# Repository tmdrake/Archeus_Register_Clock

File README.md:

# Archeus_Register_Clock
Driver and Clock for a mechanical tele-register clock.

See video: https://www.youtube.com/watch?v=ujtkTZA01rc

Frans lab did a video on it.
https://www.youtube.com/watch?v=c6l2vbn6IXM&t=259s

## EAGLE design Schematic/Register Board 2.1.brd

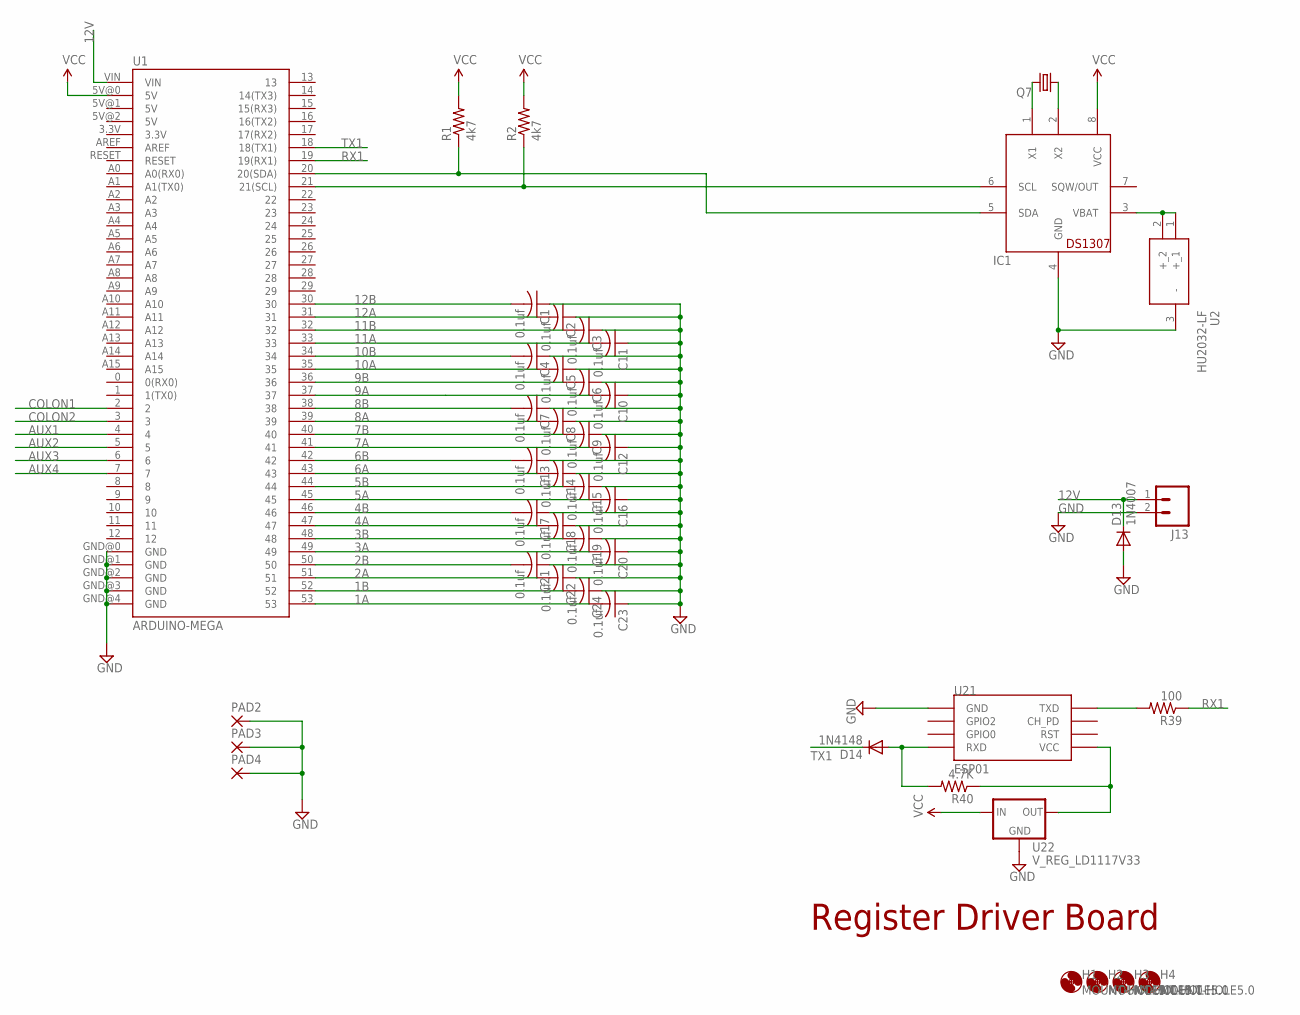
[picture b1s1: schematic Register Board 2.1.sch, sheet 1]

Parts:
C1, C2, C3, C4, C5, C6, C7, C8, C9, C10, C11, C12, C13, C14, C15, C16, C17, C18, C19, C20, C21, C22, C23, C24: 0.1uf; C025-025X050
D13: 1N4007; DO41-10
D14: 1N4148; DO35-10
H1, H2, H3, H4: MOUNT-HOLE5.0; 5,0
IC1: DS1307; DIL08
J13: M025MM; SCREWTERMINAL-5MM-2
PAD2, PAD3, PAD4: 1,6/0,8
Q7: CRYSTALTC26H; TC26H
R1, R2: 4k7; 0204/7
R39: 100; 0204/7
R40: 4.7K; 0204/7
U1: ARDUINO-MEGA; ARDUINO_MEGA_PINSONLY
U2: HU2032-LF; HU2032LF
U21: ESP01
U22: V_REG_LD1117V33; 78XXL

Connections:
1A: C23.2, U1.53; also elsewhere on the board
1B: C24.2, U1.52; also elsewhere on the board
2A: C22.2, U1.51; also elsewhere on the board
2B: C21.2, U1.50; also elsewhere on the board
3A: C20.2, U1.49; also elsewhere on the board
3B: C19.2, U1.48; also elsewhere on the board
4A: C18.2, U1.47; also elsewhere on the board
4B: C17.2, U1.46; also elsewhere on the board
5A: C16.2, U1.45; also elsewhere on the board
5B: C15.2, U1.44; also elsewhere on the board
6A: C14.2, U1.43; also elsewhere on the board
6B: C13.2, U1.42; also elsewhere on the board
7A: C12.2, U1.41; also elsewhere on the board
7B: C9.2, U1.40; also elsewhere on the board
8A: C8.2, U1.39; also elsewhere on the board
8B: C7.2, U1.38; also elsewhere on the board
9A: U1.37; also elsewhere on the board
9B: C6.2, U1.36; also elsewhere on the board
10A: C5.2, U1.35; also elsewhere on the board
10B: C4.2, U1.34; also elsewhere on the board
11A: C11.2, U1.33; also elsewhere on the board
11B: C3.2, U1.32; also elsewhere on the board
12A: C2.2, U1.31; also elsewhere on the board
12B: C1.2, U1.30; also elsewhere on the board
12V: D13.C, J13.1, U1.VIN; also elsewhere on the board
AUX1: U1.4; also elsewhere on the board
AUX2: U1.5; also elsewhere on the board
AUX3: U1.6; also elsewhere on the board
AUX4: U1.7; also elsewhere on the board
COLON1: U1.2; also elsewhere on the board
COLON2: U1.3; also elsewhere on the board
GND: C1.1, C2.1, C3.1, C4.1, C5.1, C6.1, C7.1, C8.1, C9.1, C10.1, C11.1, C12.1, C13.1, C14.1, C15.1, C16.1, C17.1, C18.1, C19.1, C20.1, C21.1, C22.1, C23.1, C24.1, D13.A, IC1.4 (GND), J13.2, PAD2.1, PAD3.1, PAD4.1, U1.GND@0 (GND), U1.GND@1 (GND), U1.GND@2 (GND), U1.GND@3 (GND), U1.GND@4 (GND), U2.3 (-), U21.GND, U22.IN (GND); also elsewhere on the board
unnamed: IC1.5 (SDA), R1.1, U1.20 (20(SDA))
unnamed: IC1.6 (SCL), R2.1, U1.21 (21(SCL))
unnamed: IC1.2 (X2), Q7.1
unnamed: IC1.1 (X1), Q7.2
unnamed: IC1.3 (VBAT), U2.1 (+_1), U2.2 (+_2)
unnamed: R39.2, U21.TX (TXD)
unnamed: R40.1, U21.VCC, U22.GND (OUT)
unnamed: D14.A, R40.2, U21.RX (RXD)
RX1: R39.1, U1.19 (19(RX1))
TX1: D14.C, U1.18 (18(TX1))
VCC: IC1.8 (VCC), R1.2, R2.2, U1.5V@0 (5V), U22.OUT (IN)

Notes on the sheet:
Register Driver Board

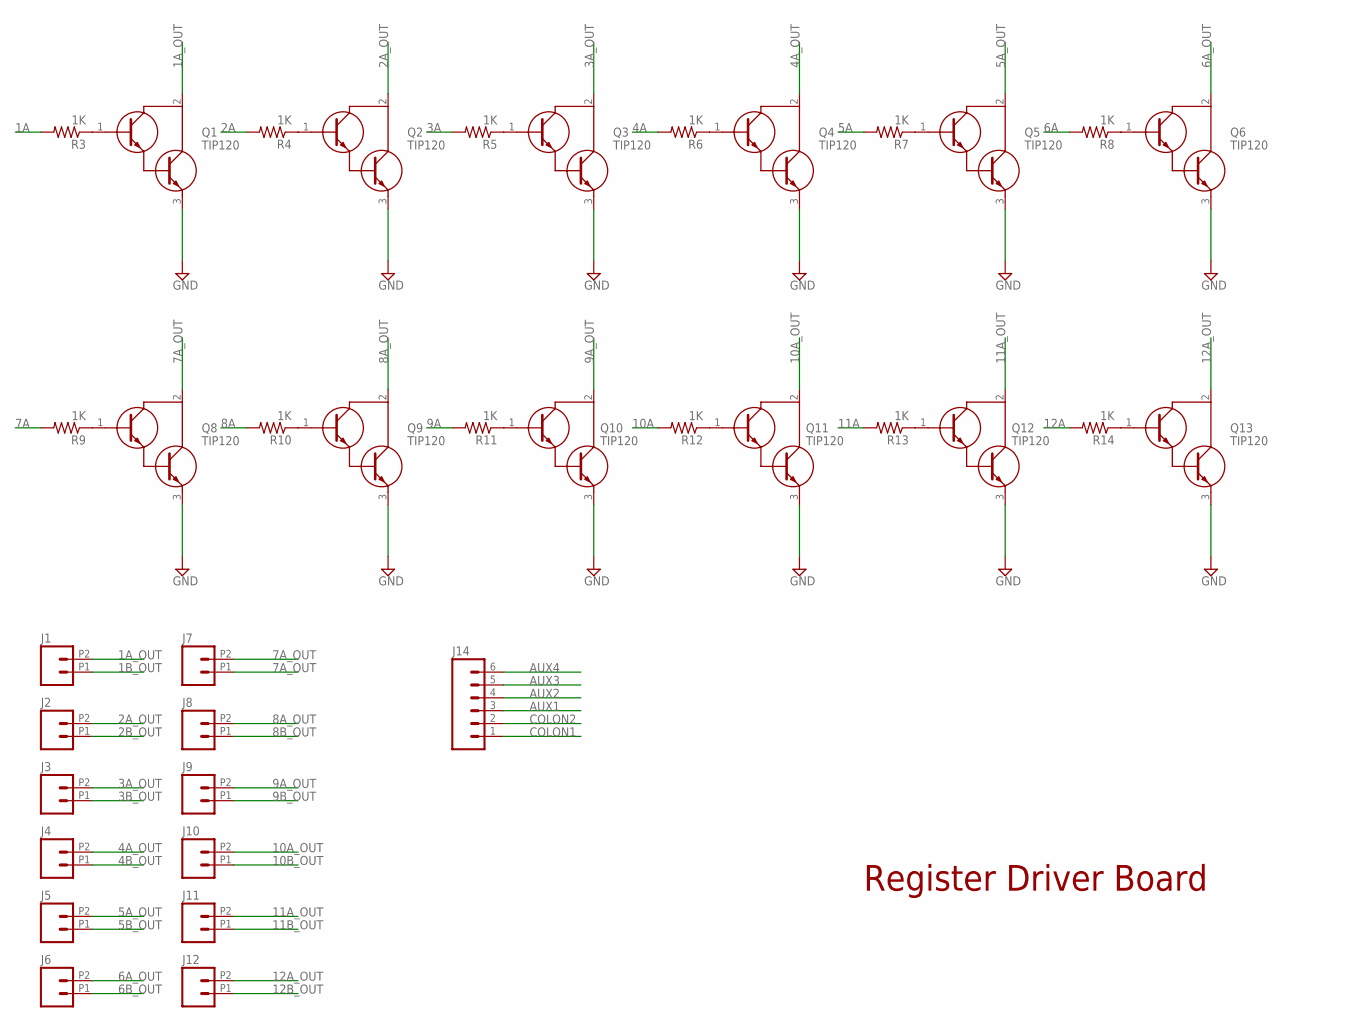
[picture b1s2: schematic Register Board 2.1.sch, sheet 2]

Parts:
J1, J2, J3, J4, J5, J6, J7, J8, J9, J10, J11, J12: M022.54MM_SCREWTERM; 1X02_2.54_SCREWTERM
J14: M06LOCK; 1X06_LOCK
Q1, Q2, Q3, Q4, Q5, Q6, Q8, Q9, Q10, Q11, Q12, Q13: TIP120; TO255P460X1020X2008-3P
R3, R4, R5, R6, R7, R8, R9, R10, R11, R12, R13, R14: 1K; 0204/7

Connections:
1A: R3.2; also elsewhere on the board
1A_OUT: J1.P2 (2), Q1.2 (C)
1B_OUT: J1.P1 (1); also elsewhere on the board
2A: R4.2; also elsewhere on the board
2A_OUT: J2.P2 (2), Q2.2 (C)
2B_OUT: J2.P1 (1); also elsewhere on the board
3A: R5.2; also elsewhere on the board
3A_OUT: J3.P2 (2), Q3.2 (C)
3B_OUT: J3.P1 (1); also elsewhere on the board
4A: R6.2; also elsewhere on the board
4A_OUT: J4.P2 (2), Q4.2 (C)
4B_OUT: J4.P1 (1); also elsewhere on the board
5A: R7.2; also elsewhere on the board
5A_OUT: J5.P2 (2), Q5.2 (C)
5B_OUT: J5.P1 (1); also elsewhere on the board
6A: R8.2; also elsewhere on the board
6A_OUT: J6.P2 (2), Q6.2 (C)
6B_OUT: J6.P1 (1); also elsewhere on the board
7A: R9.2; also elsewhere on the board
7A_OUT: J7.P1 (1), J7.P2 (2), Q8.2 (C)
8A: R10.2; also elsewhere on the board
8A_OUT: J8.P2 (2), Q9.2 (C)
8B_OUT: J8.P1 (1); also elsewhere on the board
9A: R11.2; also elsewhere on the board
9A_OUT: J9.P2 (2), Q10.2 (C)
9B_OUT: J9.P1 (1); also elsewhere on the board
10A: R12.2; also elsewhere on the board
10A_OUT: J10.P2 (2), Q11.2 (C)
10B_OUT: J10.P1 (1); also elsewhere on the board
11A: R13.2; also elsewhere on the board
11A_OUT: J11.P2 (2), Q12.2 (C)
11B_OUT: J11.P1 (1); also elsewhere on the board
12A: R14.2; also elsewhere on the board
12A_OUT: J12.P2 (2), Q13.2 (C)
12B_OUT: J12.P1 (1)
AUX1: J14.3; also elsewhere on the board
AUX2: J14.4; also elsewhere on the board
AUX3: J14.5; also elsewhere on the board
AUX4: J14.6; also elsewhere on the board
COLON1: J14.1; also elsewhere on the board
COLON2: J14.2; also elsewhere on the board
GND: Q1.3 (E), Q2.3 (E), Q3.3 (E), Q4.3 (E), Q5.3 (E), Q6.3 (E), Q8.3 (E), Q9.3 (E), Q10.3 (E), Q11.3 (E), Q12.3 (E), Q13.3 (E); also elsewhere on the board
unnamed: Q1.1 (B), R3.1
unnamed: Q2.1 (B), R4.1
unnamed: Q3.1 (B), R5.1
unnamed: Q4.1 (B), R6.1
unnamed: Q5.1 (B), R7.1
unnamed: Q6.1 (B), R8.1
unnamed: Q8.1 (B), R9.1
unnamed: Q9.1 (B), R10.1
unnamed: Q10.1 (B), R11.1
unnamed: Q11.1 (B), R12.1
unnamed: Q12.1 (B), R13.1
unnamed: Q13.1 (B), R14.1

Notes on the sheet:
Register Driver Board

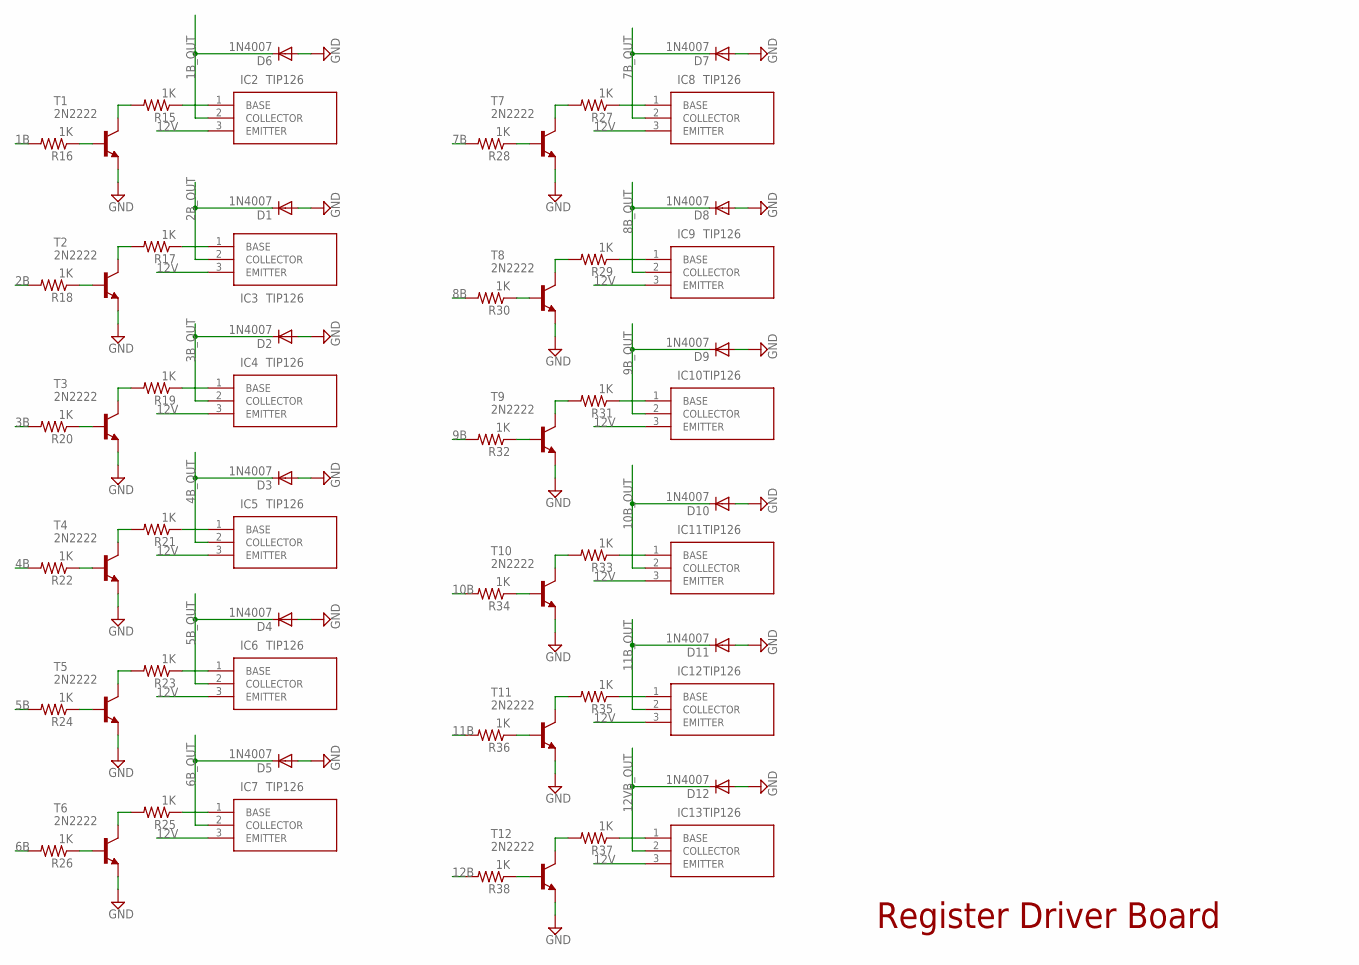
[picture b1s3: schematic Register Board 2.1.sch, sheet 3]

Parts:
D1, D2, D3, D4, D5, D6, D7, D8, D9, D10, D11, D12: 1N4007; DO41-10
IC2, IC3, IC4, IC5, IC6, IC7, IC8, IC9, IC10, IC11, IC12, IC13: TIP126; TO304P498X1010X2089-3P
R15, R16, R17, R18, R19, R20, R21, R22, R23, R24, R25, R26, R27, R28, R29, R30, R31, R32, R33, R34, R35, R36, R37, R38: 1K; 0204/7
T1, T2, T3, T4, T5, T6, T7, T8, T9, T10, T11, T12: 2N2222; TO92-EBC-OVAL

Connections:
1B: R16.2; also elsewhere on the board
1B_OUT: D6.C, IC2.2 (COLLECTOR); also elsewhere on the board
2B: R18.2; also elsewhere on the board
2B_OUT: D1.C, IC3.2 (COLLECTOR); also elsewhere on the board
3B: R20.2; also elsewhere on the board
3B_OUT: D2.C, IC4.2 (COLLECTOR); also elsewhere on the board
4B: R22.2; also elsewhere on the board
4B_OUT: D3.C, IC5.2 (COLLECTOR); also elsewhere on the board
5B: R24.2; also elsewhere on the board
5B_OUT: D4.C, IC6.2 (COLLECTOR); also elsewhere on the board
6B: R26.2; also elsewhere on the board
6B_OUT: D5.C, IC7.2 (COLLECTOR); also elsewhere on the board
7B: R28.2; also elsewhere on the board
7B_OUT: D7.C, IC8.2 (COLLECTOR)
8B: R30.2; also elsewhere on the board
8B_OUT: D8.C, IC9.2 (COLLECTOR); also elsewhere on the board
9B: R32.2; also elsewhere on the board
9B_OUT: D9.C, IC10.2 (COLLECTOR); also elsewhere on the board
10B: R34.2; also elsewhere on the board
10B_OUT: D10.C, IC11.2 (COLLECTOR); also elsewhere on the board
11B: R36.2; also elsewhere on the board
11B_OUT: D11.C, IC12.2 (COLLECTOR); also elsewhere on the board
12B: R38.2; also elsewhere on the board
12V: IC2.3 (EMITTER), IC3.3 (EMITTER), IC4.3 (EMITTER), IC5.3 (EMITTER), IC6.3 (EMITTER), IC7.3 (EMITTER), IC8.3 (EMITTER), IC9.3 (EMITTER), IC10.3 (EMITTER), IC11.3 (EMITTER), IC12.3 (EMITTER), IC13.3 (EMITTER); also elsewhere on the board
12VB_OUT: D12.C, IC13.2 (COLLECTOR)
GND: D1.A, D2.A, D3.A, D4.A, D5.A, D6.A, D7.A, D8.A, D9.A, D10.A, D11.A, D12.A, T1.E, T2.E, T3.E, T4.E, T5.E, T6.E, T7.E, T8.E, T9.E, T10.E, T11.E, T12.E; also elsewhere on the board
unnamed: IC2.1 (BASE), R15.1
unnamed: R15.2, T1.C
unnamed: R16.1, T1.B
unnamed: IC3.1 (BASE), R17.1
unnamed: R17.2, T2.C
unnamed: R18.1, T2.B
unnamed: IC4.1 (BASE), R19.1
unnamed: R19.2, T3.C
unnamed: R20.1, T3.B
unnamed: IC5.1 (BASE), R21.1
unnamed: R21.2, T4.C
unnamed: R22.1, T4.B
unnamed: IC6.1 (BASE), R23.1
unnamed: R23.2, T5.C
unnamed: R24.1, T5.B
unnamed: IC7.1 (BASE), R25.1
unnamed: R25.2, T6.C
unnamed: R26.1, T6.B
unnamed: IC8.1 (BASE), R27.1
unnamed: R27.2, T7.C
unnamed: R28.1, T7.B
unnamed: IC9.1 (BASE), R29.1
unnamed: R29.2, T8.C
unnamed: R30.1, T8.B
unnamed: IC10.1 (BASE), R31.1
unnamed: R31.2, T9.C
unnamed: R32.1, T9.B
unnamed: IC11.1 (BASE), R33.1
unnamed: R33.2, T10.C
unnamed: R34.1, T10.B
unnamed: IC12.1 (BASE), R35.1
unnamed: R35.2, T11.C
unnamed: R36.1, T11.B
unnamed: IC13.1 (BASE), R37.1
unnamed: R37.2, T12.C
unnamed: R38.1, T12.B

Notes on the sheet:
Register Driver Board

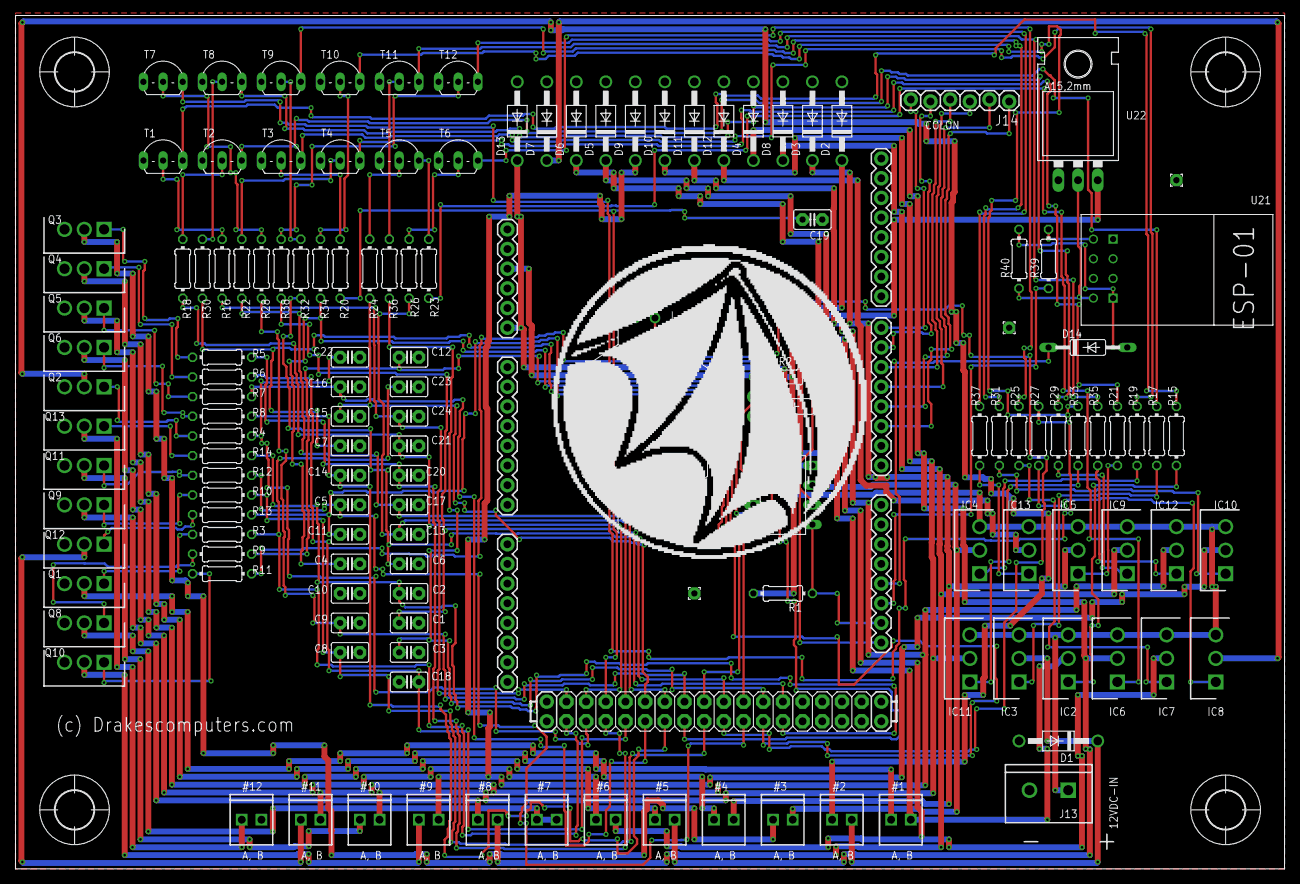
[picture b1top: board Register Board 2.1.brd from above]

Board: 2 copper layers, 163.8 x 110.2 mm, 142 parts (0 on the bottom side), 115 nets.

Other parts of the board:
U$1: DCLOGO

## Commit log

2025-01-05 Updating readme and First commit
    Nothing big just a test commit and will update as time progresses.
2025-01-05 Minor update
2025-01-07 Board Revision 2.1
    Updated the Board. Added a header for colon, buttons, etc.
2025-02-01 Updates
    Fixed Register Library removed the Delay so seconds should work correctly once the time on the register matches the RTC...
2025-02-01 Minor update
    Minor update
2025-02-02 Fixed connection to WIFI
    Added interface via Serial0(Menu) and Serial1(Sync)
2025-02-03 Updated offset
    Offset will be needed later...
2025-04-10 Added Schematics
2025-04-16 Added a DST parameter

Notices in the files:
parts and their libraries:
SparkFun-Connectors: Licensing: Creative Commons ShareAlike 4.0 International - https://creativecommons.org/licenses/by-sa/4.0
SparkFun: Licensing: CC v3.0 Share-Alike You are welcome to use this library for commercial purposes.
